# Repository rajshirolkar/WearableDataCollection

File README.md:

# Wearable Data Collection Device Project for ESP32 🚀

This repository contains individual sensor codes and a combined code for interfacing multiple sensors with an ESP32 microcontroller. The sensors used in this project are BME280, TSL2561, MLX90614, and MAX30102.

## Table of Contents 📚

- [Wearable Data Collection Device Project for ESP32 🚀](#wearable-data-collection-device-project-for-esp32-)
  - [Table of Contents 📚](#table-of-contents-)
  - [Sensor Overview 🌡💡](#sensor-overview-)
  - [Files in the Repository 📁](#files-in-the-repository-)
  - [Connection Diagrams 🔌](#connection-diagrams-)
    - [BME280 \& TSL2561](#bme280--tsl2561)
    - [MLX90614 \& MAX30102](#mlx90614--max30102)
  - [Usage 🛠](#usage-)
  - [License 📄](#license-)

## Sensor Overview 🌡💡

1. **BME280**: A temperature, humidity, and pressure sensor.
2. **TSL2561**: An ambient light sensor that measures illuminance (lux).
3. **MLX90614**: A non-contact infrared temperature sensor.
4. **MAX30102**: A pulse oximeter and heart rate sensor.

## Files in the Repository 📁

- `BME280.ino`: Code for interfacing the BME280 sensor with ESP32.
- `TSL2561.ino`: Code for interfacing the TSL2561 sensor with ESP32.
- `MLX90614.ino`: Code for interfacing the MLX90614 sensor with ESP32.
- `MAX30102.ino`: Code for interfacing the MAX30102 sensor with ESP32.
- `CombinedSensors.ino`: Combined code for interfacing all four sensors with ESP32.

## Connection Diagrams 🔌

### BME280 & TSL2561

- VCC: 3.3V
- GND: GND
- SDA: GPIO21 (SDA)
- SCL: GPIO22 (SCL)

### MLX90614 & MAX30102

- VCC: 3.3V
- GND: GND
- SDA: GPIO21 (SDA)
- SCL: GPIO22 (SCL)

## Usage 🛠

1. Clone or download this repository.
2. Open the desired `.ino` file with the Arduino IDE.
3. Connect the corresponding sensor(s) to the ESP32 according to the connection diagrams.
4. Upload the code to your ESP32 board.
5. Open the Serial Monitor to view the sensor data.

## License 📄

This project is released under the MIT License.

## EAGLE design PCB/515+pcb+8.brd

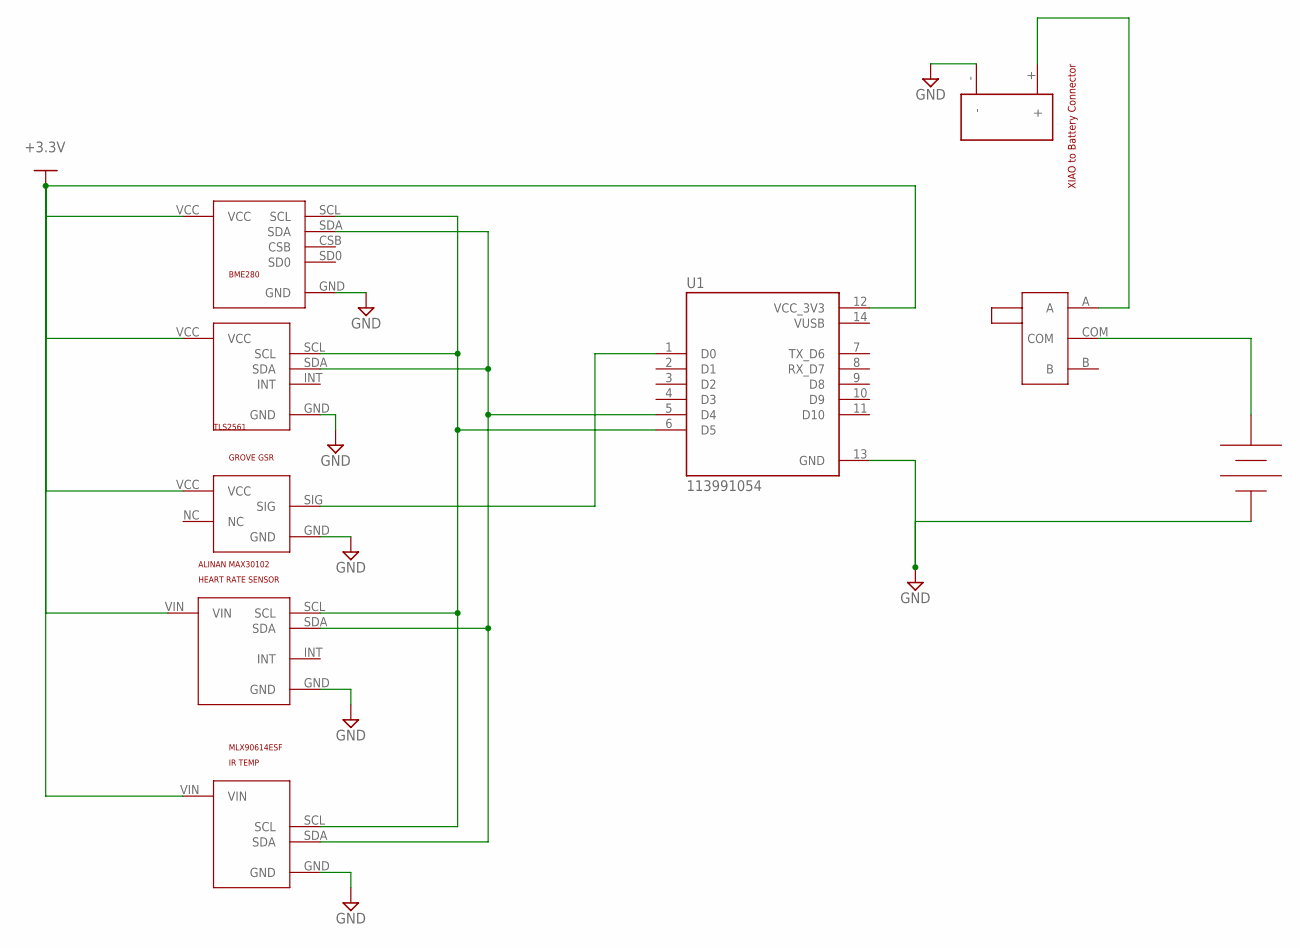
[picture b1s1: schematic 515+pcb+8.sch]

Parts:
U1: 113991054; MODULE_113991054
U$1: POWER_BREAKOUT
U$2: GROVE_GSR
U$3: BME280
U$4: MLX90614ESF
U$5: TLS2561; TSL2561
U$6: MAX30102_ALINAN
U$7: LIPO_BATTERY; JST_PH
U$8: SPST_SWITCH

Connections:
+3.3V: U1.12 (VCC_3V3), U$2.VCC, U$3.VCC, U$4.VIN, U$5.VCC, U$6.VIN
GND: U1.13 (GND), U$1.-, U$2.GND, U$3.GND, U$4.GND, U$5.GND, U$6.GND, U$7.GND (NEG)
unnamed: U1.6 (D5), U$3.SCL, U$4.SCL, U$5.SCL, U$6.SCL
unnamed: U1.5 (D4), U$3.SDA, U$4.SDA, U$5.SDA, U$6.SDA
unnamed: U1.1 (D0), U$2.SIG
unnamed: U$7.POS, U$8.COM
unnamed: U$1.+, U$8.A
VUSB: U1.14 (VUSB)

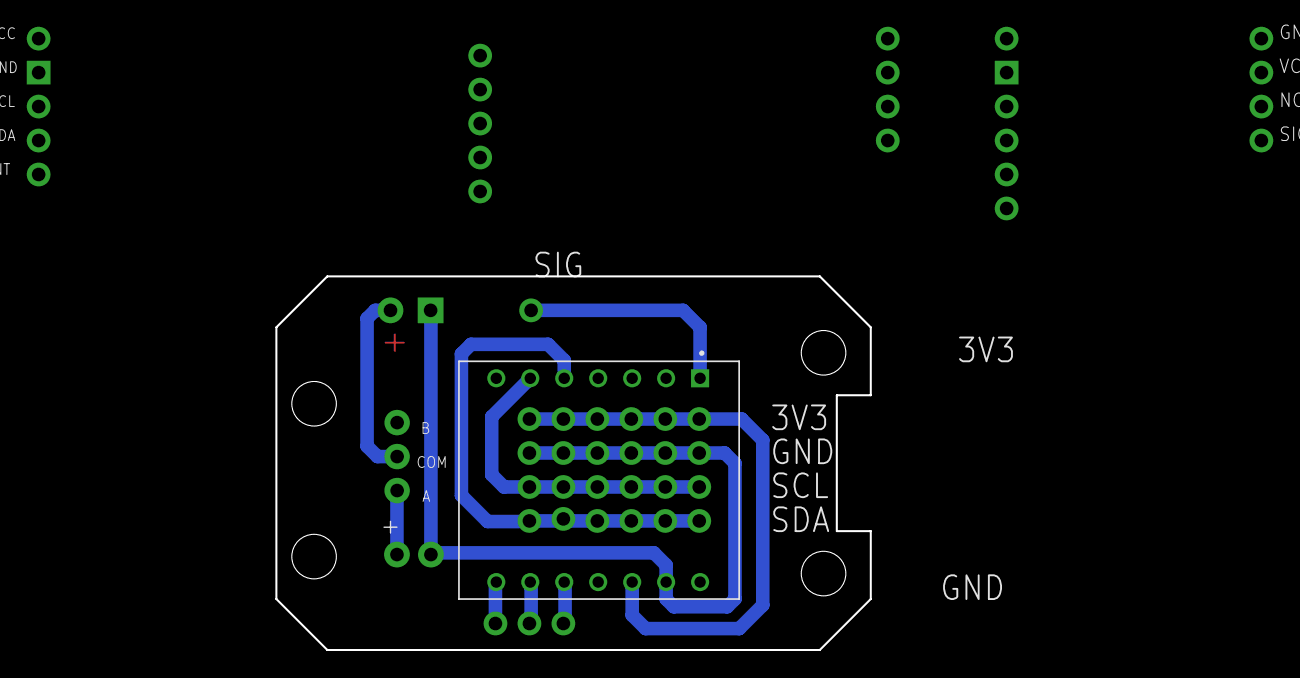
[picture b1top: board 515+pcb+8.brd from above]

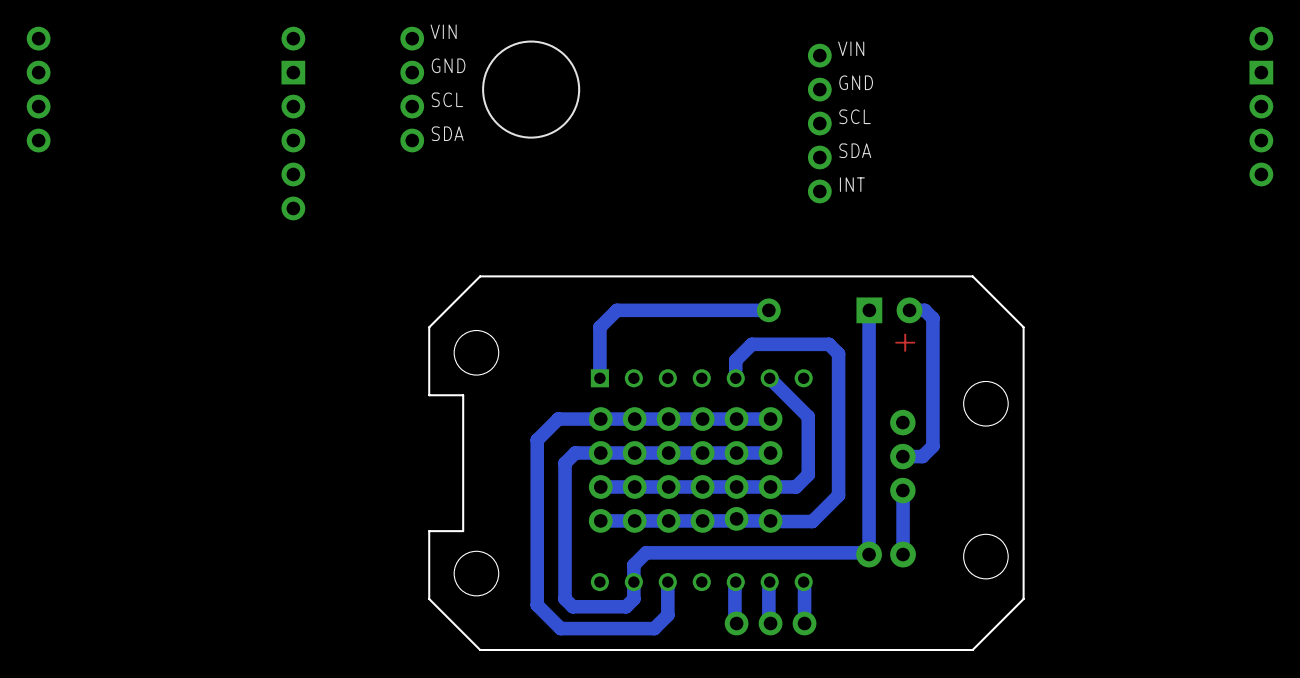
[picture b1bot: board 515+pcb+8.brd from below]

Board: 2 copper layers, 44.4 x 27.9 mm, 9 parts (2 on the bottom side), 7 nets.

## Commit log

2023-04-15 combined code
2023-04-15 added code for ambient temperature sensor and light sensor
2023-04-15 added code for heartrate and infrared temperature sensors
2023-04-15 Added Readme
2023-04-15 chore : cleanup
2023-04-15 emojis in readme!
2023-04-24 Added FastAPI code
2023-04-24 chore : housekeeping
2023-04-29 added code for GSR skin response sensor
2023-05-06 Added code for combined sensors
2023-05-10 Updated BLE code
2023-05-29 Divide the data into chunks while sending to FE
2023-06-04 mock ble code to test communication
2023-06-04 string less than 20 bytes optimization
2023-06-05 Added ESP32 final codes
2023-06-05 added PCB files
2023-06-05 chore: file moved
2023-06-07 ble test code
2023-06-07 addded requirements file
